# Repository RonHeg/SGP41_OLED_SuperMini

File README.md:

The Evs-2 SGP41 OLED SuperMini is a small PCB from RJ Hegler Technologies, LLC containing Temperature, Humidity, Pressure, VOC and NOx sensors designed to connect to the ESP32C3 SuperMini microcontroller. The PCB is also configurable to easily attach to a XIAO microcontroller or, 
with jumper wires, you could attach it to other processors.

The sensors are: Sensirion AG SHT-40-AD1B Temperature and Humidity. Sensirion AG SGP41-D-R4 NOx and VOC. TDK ICP-10111 Barometric pressure and temperature. The PCB uses its hosts 3.3v supply (~11mA with the pre-loaded software) and communicates via I2C.

EVs-2_SGP41_VOC.ino sends data thru the serial port at a baud rate of 115,200 and also displays 4 lines on a OLED display (if you are using a different display, please verify pinout, some OLED displays have Vcc and GND reversed).
The OLED display reads:

	SGP41 VOC Sensor
	78.23F, RH 48.00%
	NOx = 1, VOC = 94
	28.97inHg
 
(Numbers in the data are an example, your readings should be the actual for your conditions)

Example of data sent through the serial port is:

------------------------------

SHT40

T: 26.32        RH: 28.41

Tticks: 26704   RHticks: 18016

SGP41

compensationRh: 18016   compensationT: 26704

raw VOC Index: 28689    raw NOx Index: 0

VOC Index: 0    NOx Index: 0

ICP-10111

Temperature: 27.38C

99919.05Pa      29.51inHg

Altitude: 132.09m

------------------------------

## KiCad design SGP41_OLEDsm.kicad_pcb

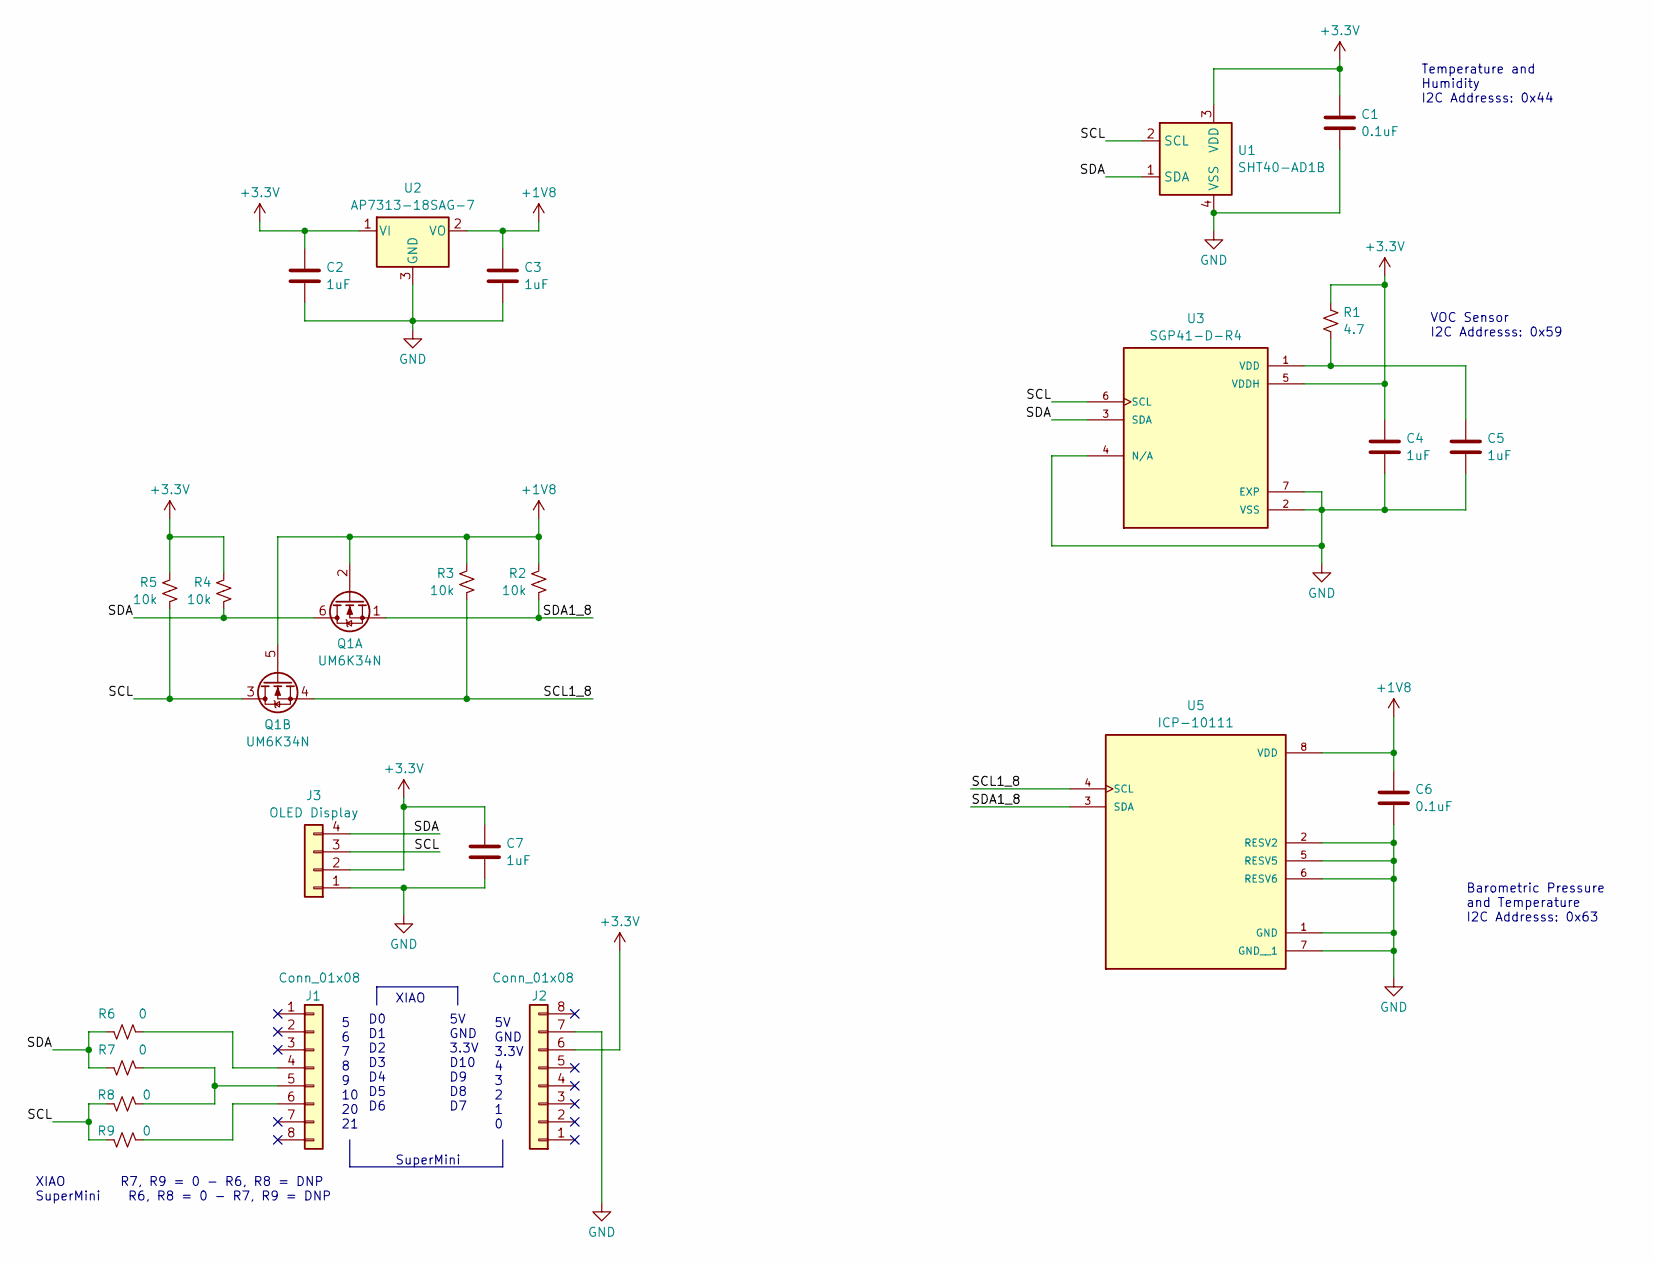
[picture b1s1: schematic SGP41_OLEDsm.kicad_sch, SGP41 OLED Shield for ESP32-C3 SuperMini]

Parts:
C1, C6: 0.1uF; C_0603_1608Metric; Manufacturer_Part_Number GCM188R71H104JA57D; JLC Pricing 0.0286
C2, C3, C4, C5, C7: 1uF; C_0603_1608Metric; Manufacturer_Part_Number C1608X5R1A105KT000E; JLC Pricing 0.0143
J1, J2: Conn_01x08; PinSocket_1x08_P2.54mm_Vertical; JLC Pricing 0.42913
J3: OLED Display; PinSocket_1x04_P2.54mm_Vertical
Q1: UM6K34N; SOT-363_SC-70-6; Manufacturer_Part_Number UM6K34N; JLC Pricing 0.0924
R1: 4.7; R_0603_1608Metric; Manufacturer_Part_Number CRCW06034R70FKEAHP; JLC Pricing 0.0857
R2, R3, R4, R5: 10k; R_0603_1608Metric; Manufacturer_Part_Number MCT06030C1002FP500; JLC Pricing 0.0157
R6, R7, R8, R9: 0; R_0603_1608Metric; Manufacturer_Part_Number CRCW06030000Z0EA; JLC Pricing .008
U1: SHT40-AD1B; Sensirion_DFN-4_1.5x1.5mm_P0.8mm_SHT4x_NoCentralPad; Manufacturer_Part_Number SHT40-AD1B-R3; JLC Pricing 1.6267
U2: AP7313-18SAG-7; SOT-23; Manufacturer_Part_Number AP7313-18SAG-7; JLC Pricing 0.1225
U3: SGP41-D-R4; XCDR_SGP40-D-R4[1]; PARTREV 1.2; JLC Pricing 6.0535
U5: ICP-10111; PSON65P250X200X100-8N; PARTREV 1.0; JLC Pricing 1.0804

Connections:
+1V8: C3.1, C6.1, Q1.2 (G), Q1.5 (G), R2.1, R3.1, U2.2 (VO), U5.8 (VDD)
+3.3V: C1.1, C2.1, C4.1, C7.1, J2.6, J3.2, R1.1, R4.1, R5.1, U1.3 (VDD), U2.1 (VI), U3.5 (VDDH)
/SCL: J3.3, Q1.3 (D), R5.2, R8.1, R9.1, U1.2 (SCL), U3.6 (SCL)
/SCL1_8: Q1.4 (S), R3.2, U5.4 (SCL)
/SDA: J3.4, Q1.6 (D), R4.2, R6.1, R7.1, U1.1 (SDA), U3.3 (SDA)
/SDA1_8: Q1.1 (S), R2.2, U5.3 (SDA)
GND: C1.2, C2.2, C3.2, C4.2, C5.2, C6.2, C7.2, J2.7, J3.1, U1.4 (VSS), U2.3 (GND), U3.2 (VSS), U3.4 (N/A), U3.7 (EXP), U5.1 (GND), U5.2 (RESV2), U5.5 (RESV5), U5.6 (RESV6), U5.7 (GND__1)
unnamed: J1.4, R6.2
unnamed: J1.5, R7.2, R8.2
unnamed: J1.6, R9.2
unnamed: C5.1, R1.2, U3.1 (VDD)

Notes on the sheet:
XIAO R7, R9 = 0 - R6, R8 = DNP SuperMini R6, R8 = 0 - R7, R9 = DNP
5V GND 3.3V D10 D9 D8 D7
D0 D1 D2 D3 D4 D5 D6
XIAO
Barometric Pressure and Temperature I2C Addresss: 0x63
SuperMini
5V GND 3.3V 4 3 2 1 0
5 6 7 8 9 10 20 21
VOC Sensor I2C Addresss: 0x59
Temperature and Humidity I2C Addresss: 0x44

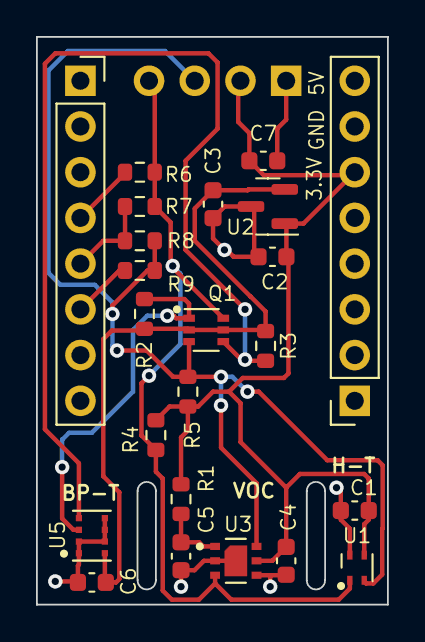
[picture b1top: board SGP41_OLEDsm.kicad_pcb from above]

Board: 2 copper layers, 19.5 x 31.5 mm, 24 parts (1 on the bottom side), 11 nets.

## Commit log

2024-11-24 Initialization
    Initial files
2024-12-19 ino file was missing
